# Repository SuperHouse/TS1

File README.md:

Touch Switch 1
==============
Copyright 2018-2019 SuperHouse Automation Pty Ltd  www.superhouse.tv  

A simple single-channel touch switch controller with a switchmode
power supply and a linear regulator, to allow operation or input
voltages up to 28V such as a wheelchair battery.

Deliberately de-sensitised to require actual contact with the
touch pad, to prevent false triggering when a finger is held
near the pad without touching it.

Open-drain output that switches to GND via an N-MOSFET.

Features:

 * at42qt1010 touch sensor IC
 * 7-28Vdc supply voltage
 * Open-drain output
 * Power LED
 * Activity LED

You can view more online at:

  http://www.superhouse.tv/ts1

INSTALLATION
------------
The design is saved as an EAGLE project. EAGLE PCB design software is
available from www.cadsoftusa.com free for non-commercial use. To use
this project download it and place the directory containing these files
into the "eagle" directory on your computer. Then open EAGLE and
navigate to the project.

DISTRIBUTION
------------
The specific terms of distribution of this project are governed by the
license referenced below.

LICENSE
-------
Licensed under the TAPR Open Hardware License (www.tapr.org/OHL).
The "license" folder within this repository also contains a copy of
this license in plain text format.

CREDITS
-------
Designed by Jonathan Oxer (jon@oxer.com.au)

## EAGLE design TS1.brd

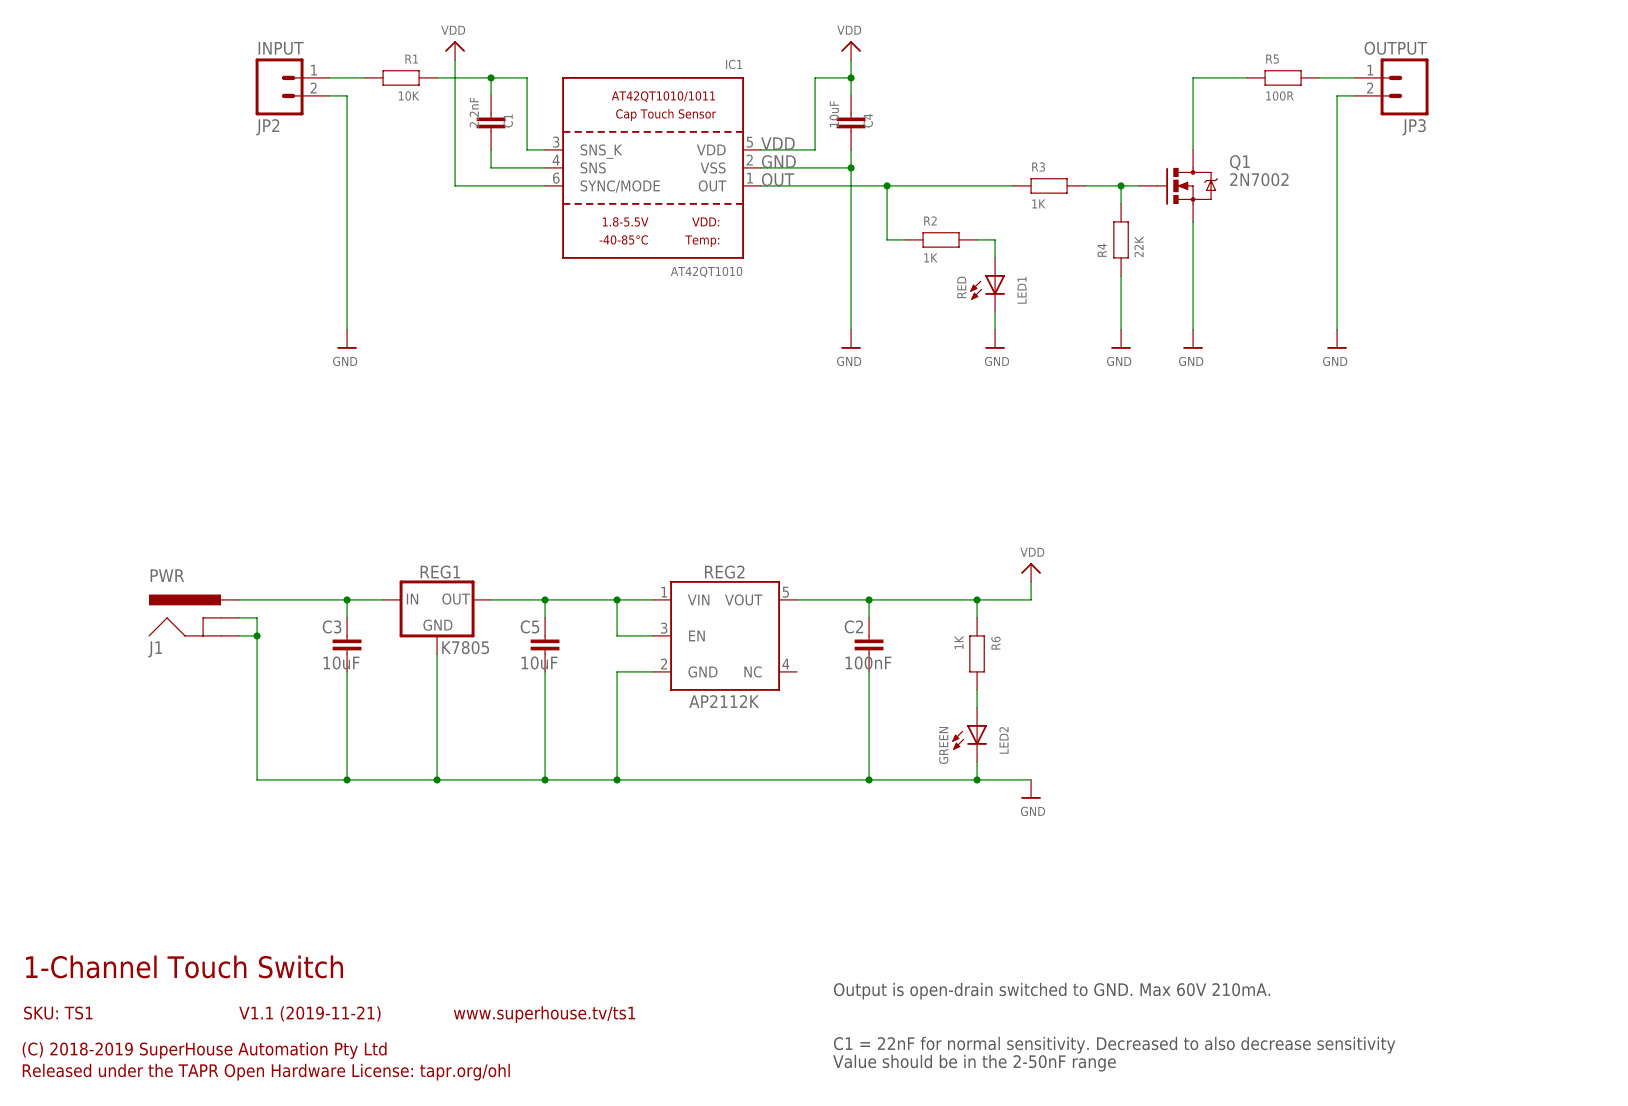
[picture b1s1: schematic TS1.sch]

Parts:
C1: 2.2nF; C0603
C2: 100nF; C0603
C3, C4, C5: 10uF; C0603
IC1: AT42QT1010; SOT23-6
J1: PWR; POWER_JACK_SLOTS
JP2: INPUT; 1X02-S
JP3: OUTPUT; 1X02-S
LED1: RED; LED-0603
LED2: GREEN; LED-0603
Q1: 2N7002; SOT23-3
R1: 10K; R0603
R2, R3, R6: 1K; R0603
R4: 22K; R0603
R5: 100R; R0603
REG1: K7805; K78XX-500R3
REG2: AP2112KSOT25; SOT23-5

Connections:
CAPPAD: JP2.1, R1.2
GND: C2.2, C3.2, C4.2, C5.2, IC1.2 (VSS), J1.GND, J1.GNDBREAK, JP2.2, JP3.2, LED1.C, LED2.C, Q1.2 (S), R4.1, REG1.2 (GND), REG2.2 (GND)
unnamed: JP3.1, R5.2
unnamed: Q1.3 (D), R5.1
unnamed: C1.2, IC1.4 (SNS)
unnamed: C1.1, IC1.3 (SNS_K), R1.1
unnamed: Q1.1 (G), R3.2, R4.2
unnamed: LED1.A, R2.2
unnamed: C3.1, J1.PWR, REG1.1 (IN)
unnamed: C5.1, REG1.3 (OUT), REG2.1 (VIN), REG2.3 (EN)
unnamed: LED2.A, R6.2
OUT: IC1.1 (OUT), R2.1, R3.1
VDD: C2.1, C4.1, IC1.5 (VDD), IC1.6 (SYNC/MODE), R6.1, REG2.5 (VOUT)

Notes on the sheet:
1-Channel Touch Switch
V1.1 (2019-11-21)
(C) 2018-2019 SuperHouse Automation Pty Ltd
Released under the TAPR Open Hardware License: tapr.org/ohl
www.superhouse.tv/ts1
SKU: TS1
C1 = 22nF for normal sensitivity. Decreased to also decrease sensitivity
Value should be in the 2-50nF range
Output is open-drain switched to GND. Max 60V 210mA.

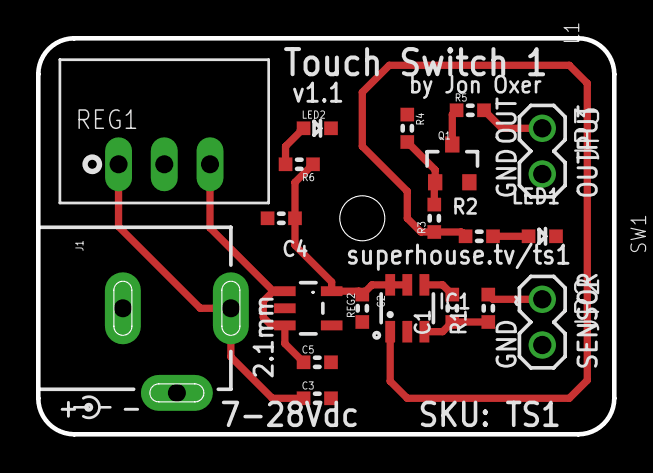
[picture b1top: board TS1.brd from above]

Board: 2 copper layers, 32.0 x 22.0 mm, 20 parts (0 on the bottom side), 13 nets.

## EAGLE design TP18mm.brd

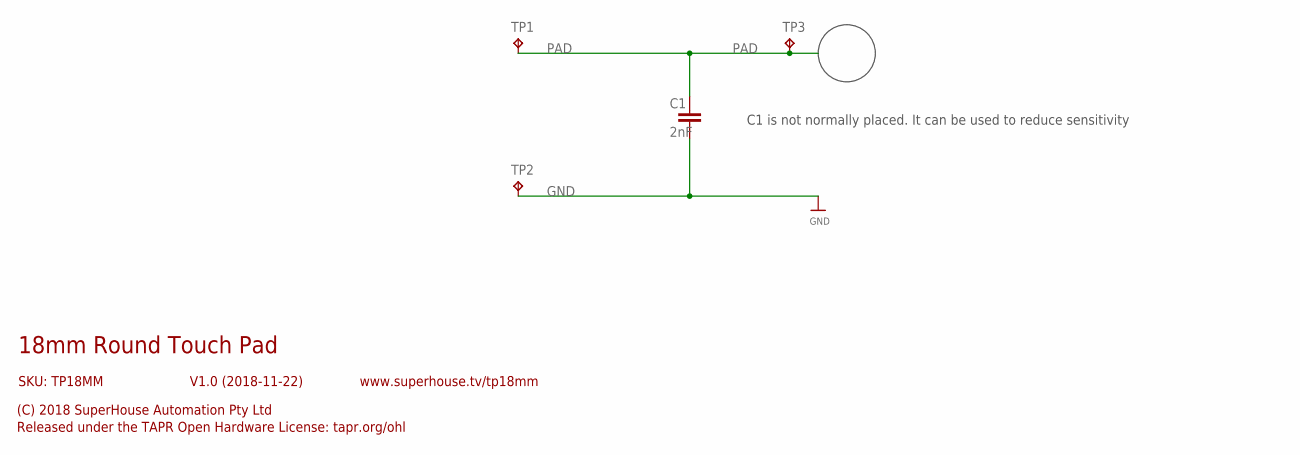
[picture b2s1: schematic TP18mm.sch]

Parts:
C1: 2nF; 0603
TP1, TP2, TP3: TPB2,54; B2,54

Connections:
GND: C1.2, TP2.TP
PAD: C1.1, TP1.TP, TP3.TP

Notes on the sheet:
18mm Round Touch Pad
V1.0 (2018-11-22)
(C) 2018 SuperHouse Automation Pty Ltd
Released under the TAPR Open Hardware License: tapr.org/ohl
www.superhouse.tv/tp18mm
SKU: TP18MM
C1 is not normally placed. It can be used to reduce sensitivity

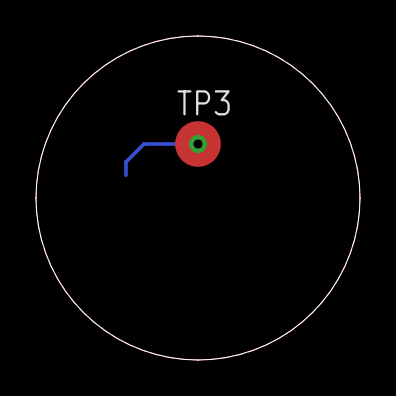
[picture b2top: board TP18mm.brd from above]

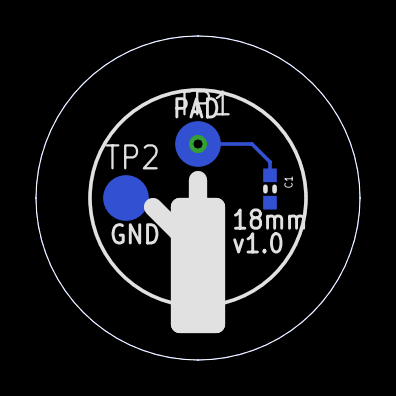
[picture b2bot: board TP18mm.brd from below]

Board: 2 copper layers, 18.0 x 18.0 mm, 4 parts (3 on the bottom side), 2 nets.

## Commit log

2018-11-21 Initial project import for v1.0 release
2018-11-21 Fixed SKU and URL in schematic
2018-11-22 Added mounting hole
2018-11-22 Added 18mm touch pad
2019-04-24 Updated footprints
2019-11-21 Pulled back GND plane around input to sensor IC to reduce capacitive loading
2019-11-21 Moved bypass cap closer to touch sensor IC

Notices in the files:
TS1.brd:
Copyright 2019
parts and their libraries:
microbuilder: This work is placed in the public domain, and may be freely used for commercial and non-commercial work with the following conditions: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
